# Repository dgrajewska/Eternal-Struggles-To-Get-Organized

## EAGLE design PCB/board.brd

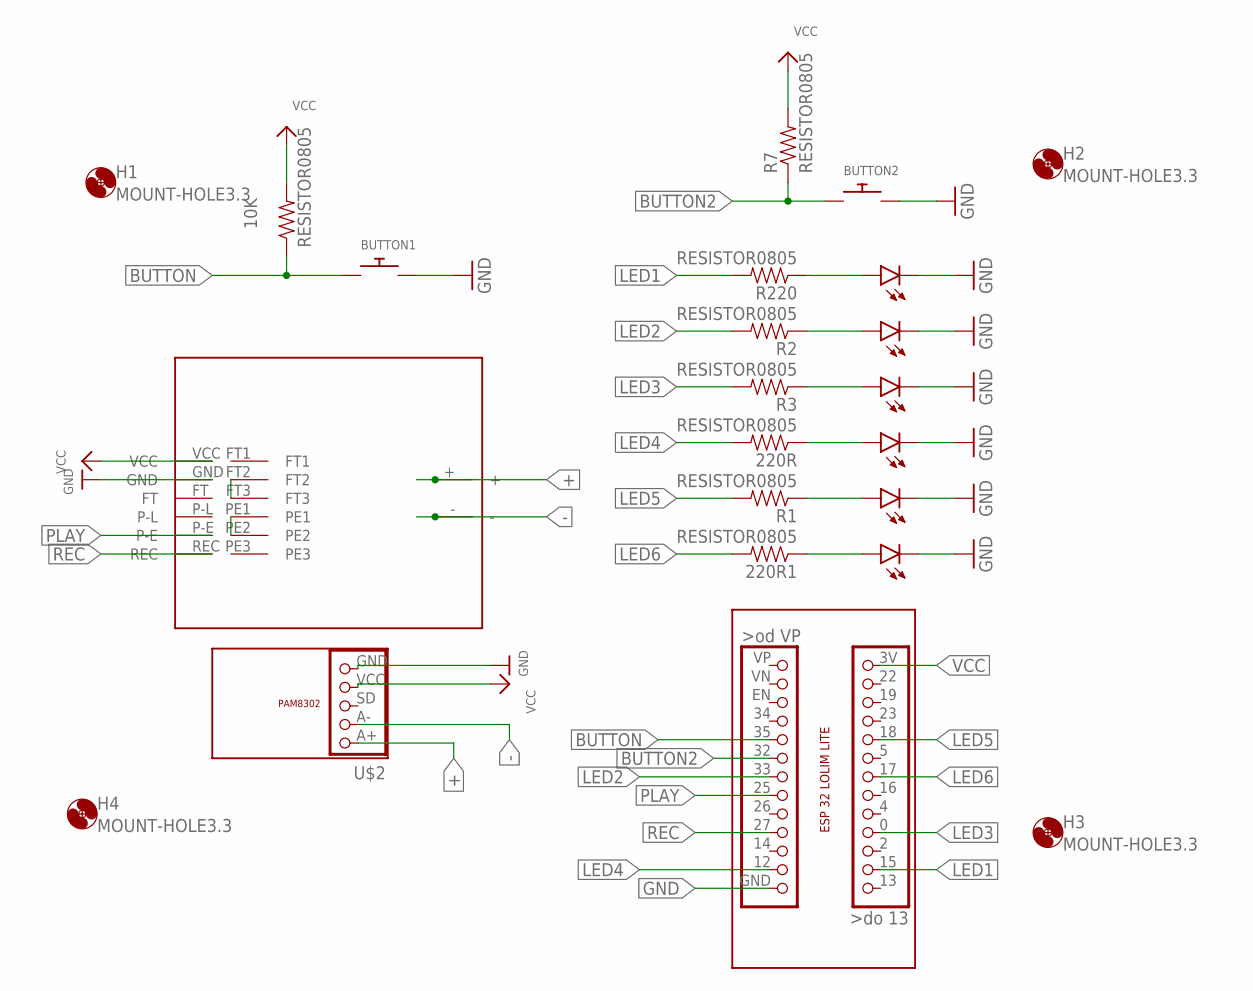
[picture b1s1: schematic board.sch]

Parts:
10K, 220R, 220R1: RESISTOR0805; R0805
BUTTON1, BUTTON2: SWITCH_PUSHBUTTONEVQ-PE; TACT_PANA-EVQ
ESP32: NOWA-ESP32
H1, H2, H3, H4: MOUNT-HOLE3.3; 3,3
LED1, LED2, LED3, LED4, LED5, LED6: LED5MM
R1, R2, R3, R7, R220: RESISTOR0805; R0805
U$2: NOWA-PAM8302
U$7: NOWA-ISD1820

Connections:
+: U$2.A+, U$7.+
-: U$2.A-, U$7.-
BUTTON: 10K.1, BUTTON1.P$1, ESP32.35
BUTTON2: BUTTON2.P$1, ESP32.32, R7.1
GND: BUTTON1.P$2, BUTTON2.P$2, ESP32.GND, LED1.K (C), LED2.K (C), LED3.K (C), LED4.K (C), LED5.K (C), LED6.K (C), U$2.GND, U$7.GND
LED1: ESP32.15, R220.2
LED2: ESP32.33, R2.2
LED3: ESP32.0, R3.2
LED4: 220R.2, ESP32.12
LED5: ESP32.18, R1.2
LED6: 220R1.2, ESP32.17
unnamed: LED5.A, R1.1
unnamed: 220R1.1, LED6.A
unnamed: LED2.A, R220.1
unnamed: LED3.A, R2.1
unnamed: LED4.A, R3.1
unnamed: 220R.1, LED1.A
unnamed: U$7.FT2, U$7.FT3
unnamed: U$7.PE1, U$7.PE2
PLAY: ESP32.25, U$7.P-E
REC: ESP32.27, U$7.REC
VCC: 10K.2, ESP32.3V, R7.2, U$2.VCC, U$7.VCC

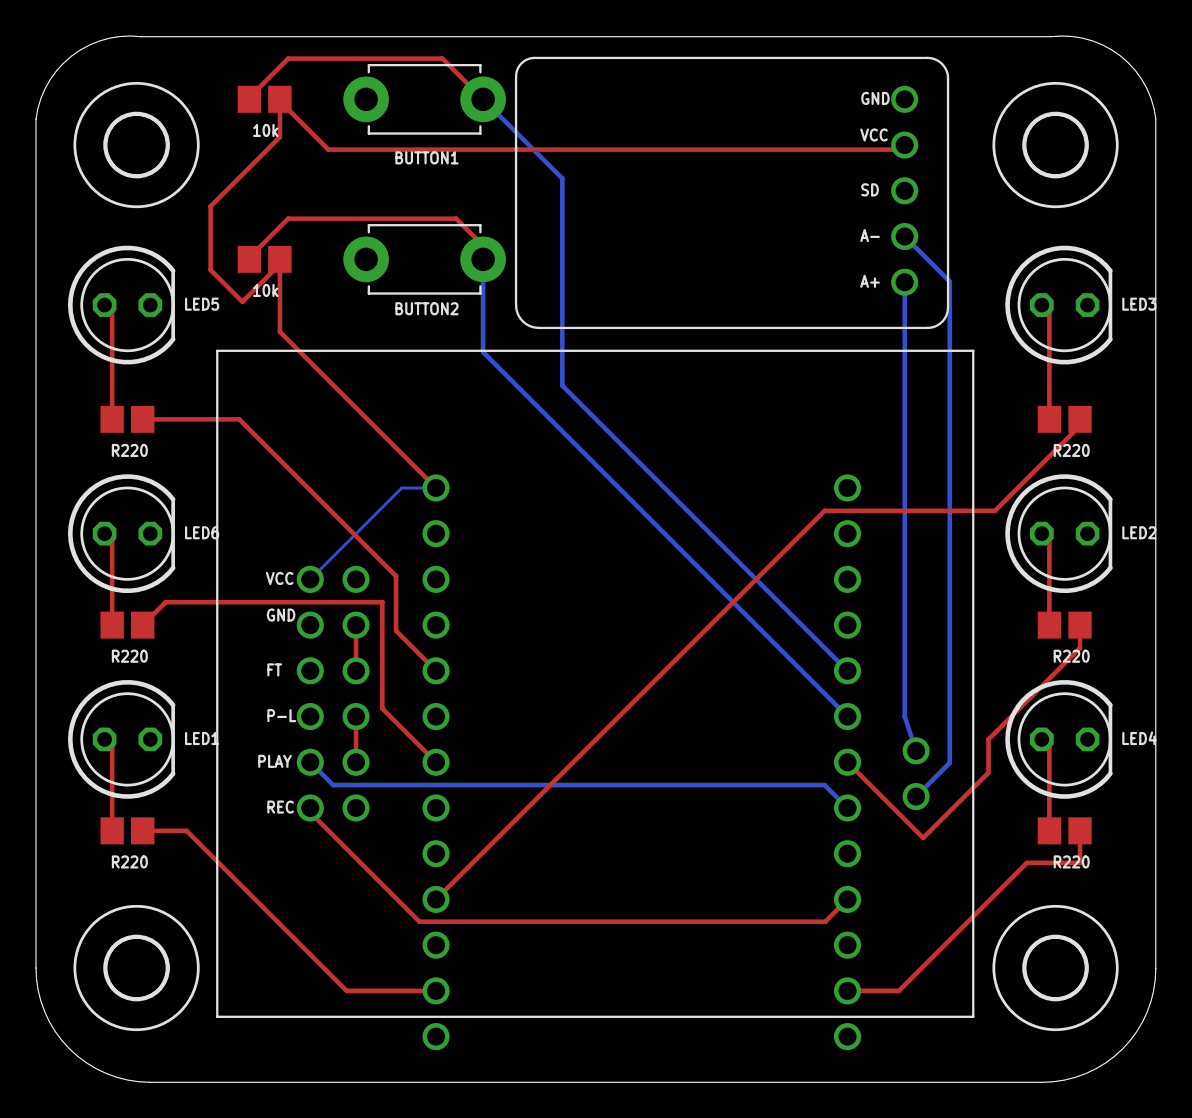
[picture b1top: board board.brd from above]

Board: 2 copper layers, 62.2 x 58.1 mm, 23 parts (1 on the bottom side), 22 nets.

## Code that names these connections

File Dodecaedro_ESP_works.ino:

// define BUTTONS
#define BUTTON 32
#define BUTTON2 14

// define ISD1820
const int REC = 27;  // pin 27 is used for recording
const int PLAY = 25; // pin 25 is used for playback-edge trigger

// define LED pins
#define LED1 = 15;
#define LED2 = 33;
#define LED3 = 0;
#define LED4 = 12;
#define LED5 = 18;
#define LED6 = 17;

// define number of led's
#define NumberOfLeds 6

uint8_t leds [] = { 15, 33, 0, 12, 18, 17 }; // list of all the leds in the array

#define EVENT_UPDATE_TIME 6000 // in milliseconds 
volatile unsigned long timingMillis = 0; // volatile will work with interrupts

// setting PWM properties
const int freq = 5000;
const int ledChannel = 0;
const int resolution = 8;

int brightnessON = 250;
int brightnessOFF = 0;

// define status to reset the loops
char status = 0;

// define button's statuses
int buttonState = 0;
int buttonState2 = 0;


void setup() {
  // begin serial communication
  Serial.begin(115200);

  // BUTTONS set up + built in resistor, no need to add any to the board
  pinMode(BUTTON, INPUT_PULLUP); //oznaczan domyslnie na pinie stan HIGH _PULLUP
  pinMode(BUTTON, INPUT_PULLUP); //oznaczan domyslnie na pinie stan HIGH _PULLUP

  // ISD1820 set up
  pinMode(REC, OUTPUT);
  pinMode(PLAY, OUTPUT);

  //LEDs set up
  for (int k = 0; k < NumberOfLeds; k++) {
    ledcAttachPin(leds[k], ledChannel);
  }

  ledcSetup (0, 5000, 8);
}


void loop() {

  // READ BUTTON VALUE
  int buttonState = digitalRead(BUTTON);

  // if button is pressed, start LED's and recording
  if (( buttonState == LOW ) && (status == 0)) {
    status = 1;
    Serial.println("button wciśnięty");

//    FADE_IN_OUT_LED ();
    LEDs_ON ();
    RECORDING ();
  }
  // if button is no pressed, LED's OFF
  else {

    ( buttonState == HIGH );
    Serial.println("button puszczony");

    LEDs_OFF ();
  }

  // RESET BUTTON STATE TO AVOID CONTINUOUS LOOP
  if (( buttonState == HIGH ) && (status == 1)) {
    status = 0;
  }

  // READ BUTTON2 VALUE
  int buttonState2 = digitalRead(BUTTON2);
  if (( buttonState2 == LOW ) && (status == 0)) {
    status = 1;
    Serial.println("button2 wciśnięty");

    LEDs_ON ();
    PLAYBACK ();

  }
  // RESET BUTTON STATE2 TO AVOID CONTINUOUS LOOP
  if (( buttonState2 == HIGH ) && (status == 1)) {
    status = 0;
  }
}

void FADE_IN_OUT_LED () {
  //BREATHING PATTERN
  
  // PWM FADE IN
  for (int dutyCycle = 0; dutyCycle <= 255; dutyCycle++) {
    ledcWrite(ledChannel, dutyCycle);
    delay(15);
  }
  // PWM FADE OUT
  for (int dutyCycle = 255; dutyCycle >= 0; dutyCycle--) {
    // changing the LED brightness with PWM
    ledcWrite(ledChannel, dutyCycle);
    delay(15);
  }
}

void LEDs_ON () {

  //ALL LEDS ON
  for ( int i = 0; i < NumberOfLeds; i++ ) {
    ledcWrite(ledChannel, brightnessON);
  }
}

void LEDs_OFF () {

  //ALL LEDS OFF
  for ( int i = 0; i < NumberOfLeds; i++ ) {
    ledcWrite(ledChannel, brightnessOFF);
  }
}

void RECORDING () {

  // FULL RECORDING FUNCTION
  digitalWrite(REC, HIGH);
  Serial.println("REC + LED started");
  delay(5000);
  digitalWrite(REC, LOW);
  Serial.println("REC finished");
}

void PLAYBACK () {

  // FULL PLAYBACK FUNCTION
  digitalWrite(PLAY, HIGH);
  Serial.println("PLAY + LED started");
  delay(5000);
  digitalWrite(PLAY, LOW);
  Serial.println("PLAY finished");
}

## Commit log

2021-06-22 Add files via upload
    Final working code for the recording device. No state machine yet.
2021-06-22 Processing files with Keystone/
2021-06-22 Create Keystone Sketch
2021-06-22 Create Prototype
2021-06-22 Create PCB
2021-06-22 Create draft
2021-07-21 switched delay for millis and added state machine

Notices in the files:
parts and their libraries:
microbuilder: This work is placed in the public domain, and may be freely used for commercial and non-commercial work with the following conditions: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
